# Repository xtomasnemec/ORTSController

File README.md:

# ORTSController
Ovladač pro OpenRailsCZ/SK podle 162/362

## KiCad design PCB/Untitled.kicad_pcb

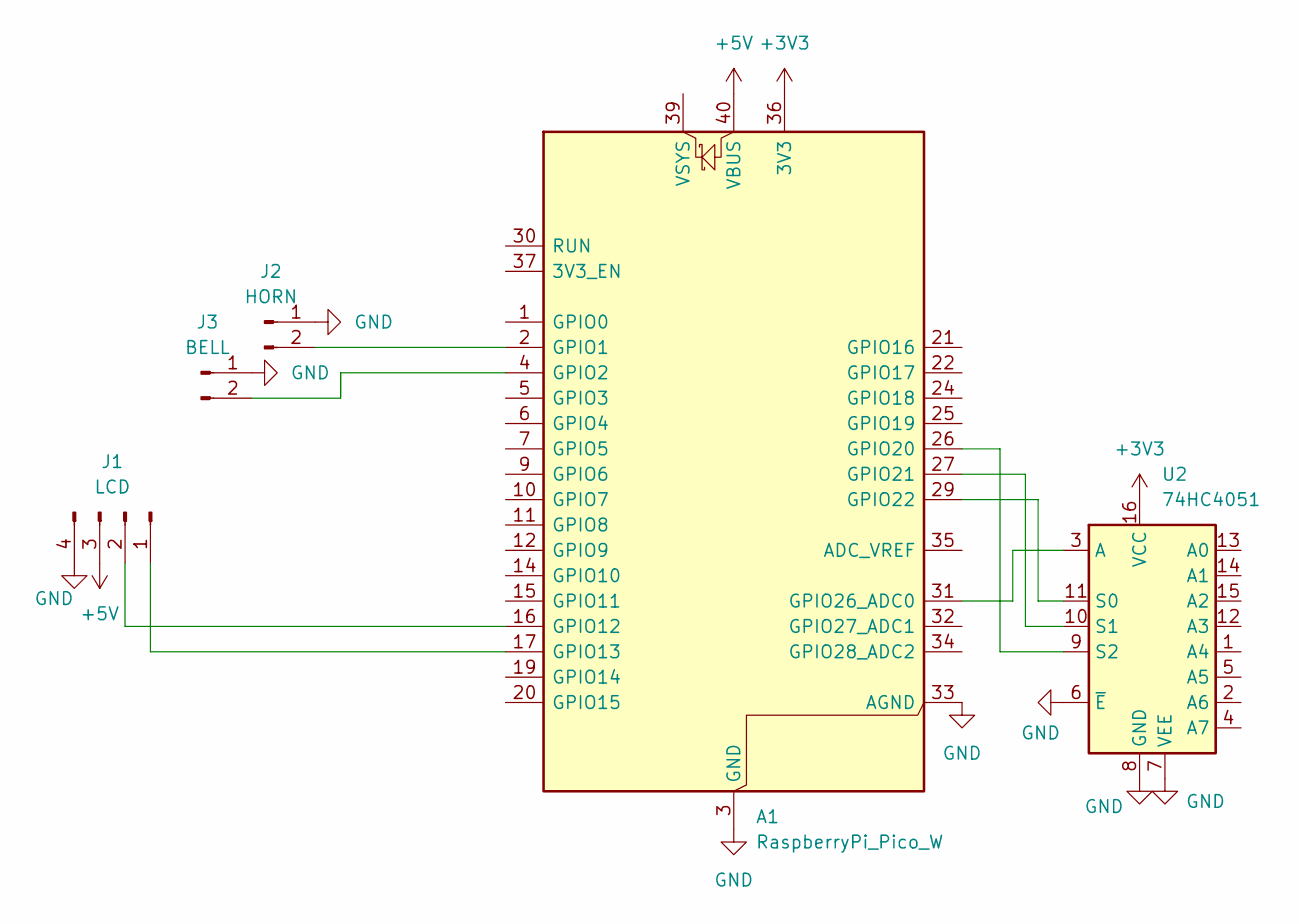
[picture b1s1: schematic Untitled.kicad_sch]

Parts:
A1: RaspberryPi_Pico_W; RaspberryPi_Pico_W_SMD_HandSolder
J1: LCD; PinHeader_1x04_P2.54mm_Vertical
J2: HORN; PinHeader_1x02_P2.54mm_Vertical
J3: BELL; PinHeader_1x02_P2.54mm_Vertical
U2: 74HC4051; DIP-16_W7.62mm

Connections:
+3V3: A1.36 (3V3), U2.16 (VCC)
+5V: A1.40 (VBUS), J1.3
GND: A1.3 (GND), A1.8 (GND), A1.13 (GND), A1.18 (GND), A1.23 (GND), A1.28 (GND), A1.33 (AGND), A1.38 (GND), J1.4, J2.1, J3.1, U2.6 (~E), U2.7 (VEE), U2.8 (GND)
unnamed: A1.2 (GPIO1), J2.2
unnamed: A1.4 (GPIO2), J3.2
unnamed: A1.16 (GPIO12), J1.2
unnamed: A1.17 (GPIO13), J1.1
unnamed: A1.26 (GPIO20), U2.9 (S2)
unnamed: A1.27 (GPIO21), U2.10 (S1)
unnamed: A1.29 (GPIO22), U2.11 (S0)
unnamed: A1.31 (GPIO26_ADC0), U2.3 (A)

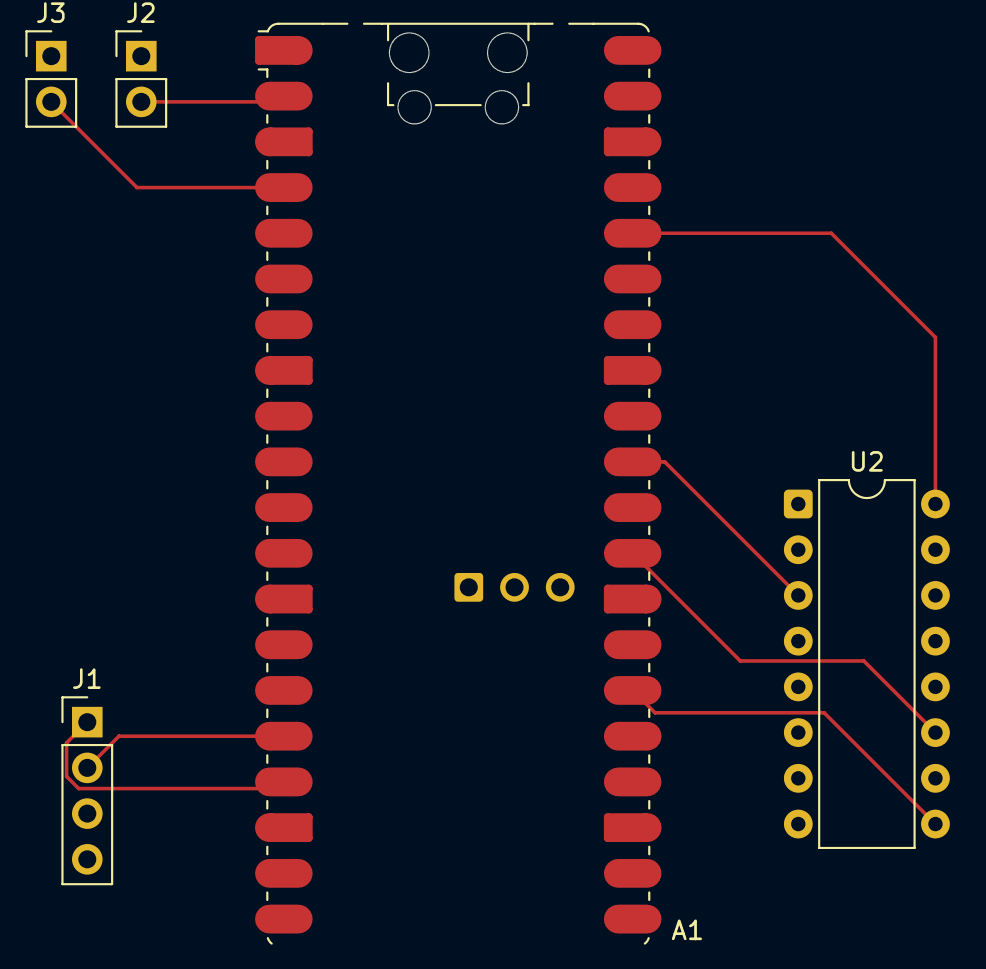
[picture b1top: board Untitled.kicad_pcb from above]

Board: 2 copper layers, 5 parts (0 on the bottom side), 11 nets.

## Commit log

2026-03-10 initial
2026-03-10 something works
